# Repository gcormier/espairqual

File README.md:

# espairqual
espairqual is an ESP32 based [esphome](https://esphome.io/) interface for [PMSx003](https://esphome.io/components/sensor/pmsx003.html) and [Panasonic NA-GCJA5](https://na.industrial.panasonic.com/products/sensors/air-quality-gas-flow-sensors/lineup/laser-type-pm-sensor/series/123557/model/123559) particulate matter (PM) sensors.

It offers a plug and play solution to integrate air quality monitoring with home assistant. It provides 5V to the sensor and 3.3V to the internal electronics.

It can be powered by USC-C, or, by a wider range of input voltages on the screw terminals. It was designed for 24VAC, but will likely work with a slightly broader range
of both AC and DC input voltages. The absolute maximum voltage for the switching regulator is 40VDC, which means up to around 28VAC. The minimum DC is approximately 9VDC.

The PCB will fit inside a [Hammond 1593KBK](https://www.hammfg.com/part/1593KBK) case. You can either cut (CNC) or 3D-print the faceplates. I have superglue'd some magnets inside the case so it can stick to my ductwork, although this attenuates the WiFi signal *alot*.

## Programming
The USB-C port can be used to program. The first time, the reset button must be held. After this, all subsequent programming does not require access to the button.

There is also a header for the typical serial flashing with GPIO0(9) and EN exposed. It follows my [eflashy32](https://github.com/gcormier/eflashy32) pinout.

## Panasonic SN-GCJA5
I contributed native support for the SN-GCJA5 [to esphome](https://esphome.io/components/sensor/gcja5.html). While the PMS5003 is a good sensor, I did receive one dead-on-arrival from Aliexpress. The Panasonic sensor is cheaper, smaller, available from tier-1 distributors (eg. [Digikey](https://www.digikey.ca/en/products/detail/panasonic-electronic-components/SN-GCJA5/10443899)) and has a 5+ year life expectancy. It has internal compensation for the fan, photo diode and laser diode.

The connector is JST-GH (1.25mm) series.

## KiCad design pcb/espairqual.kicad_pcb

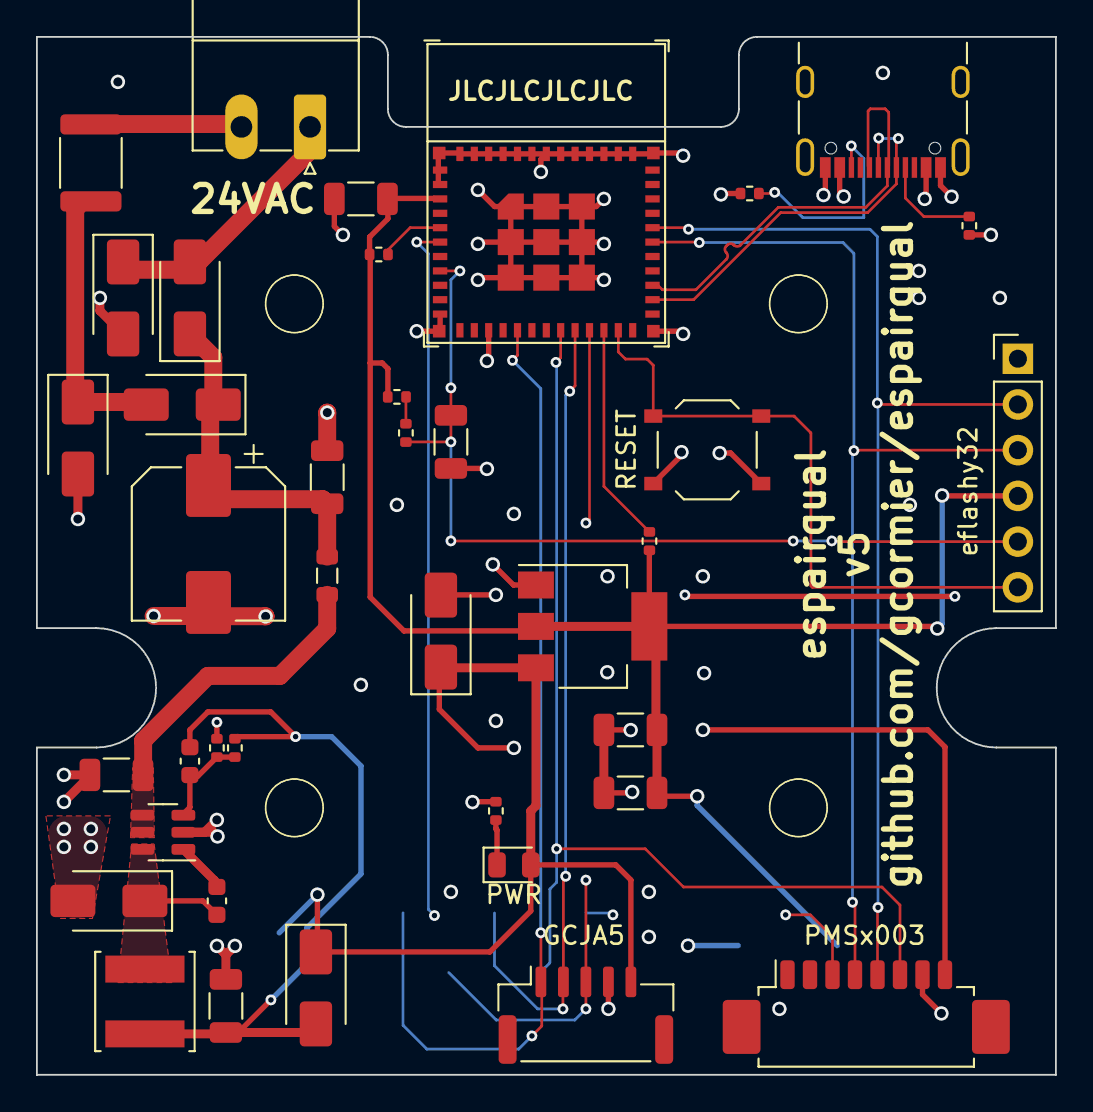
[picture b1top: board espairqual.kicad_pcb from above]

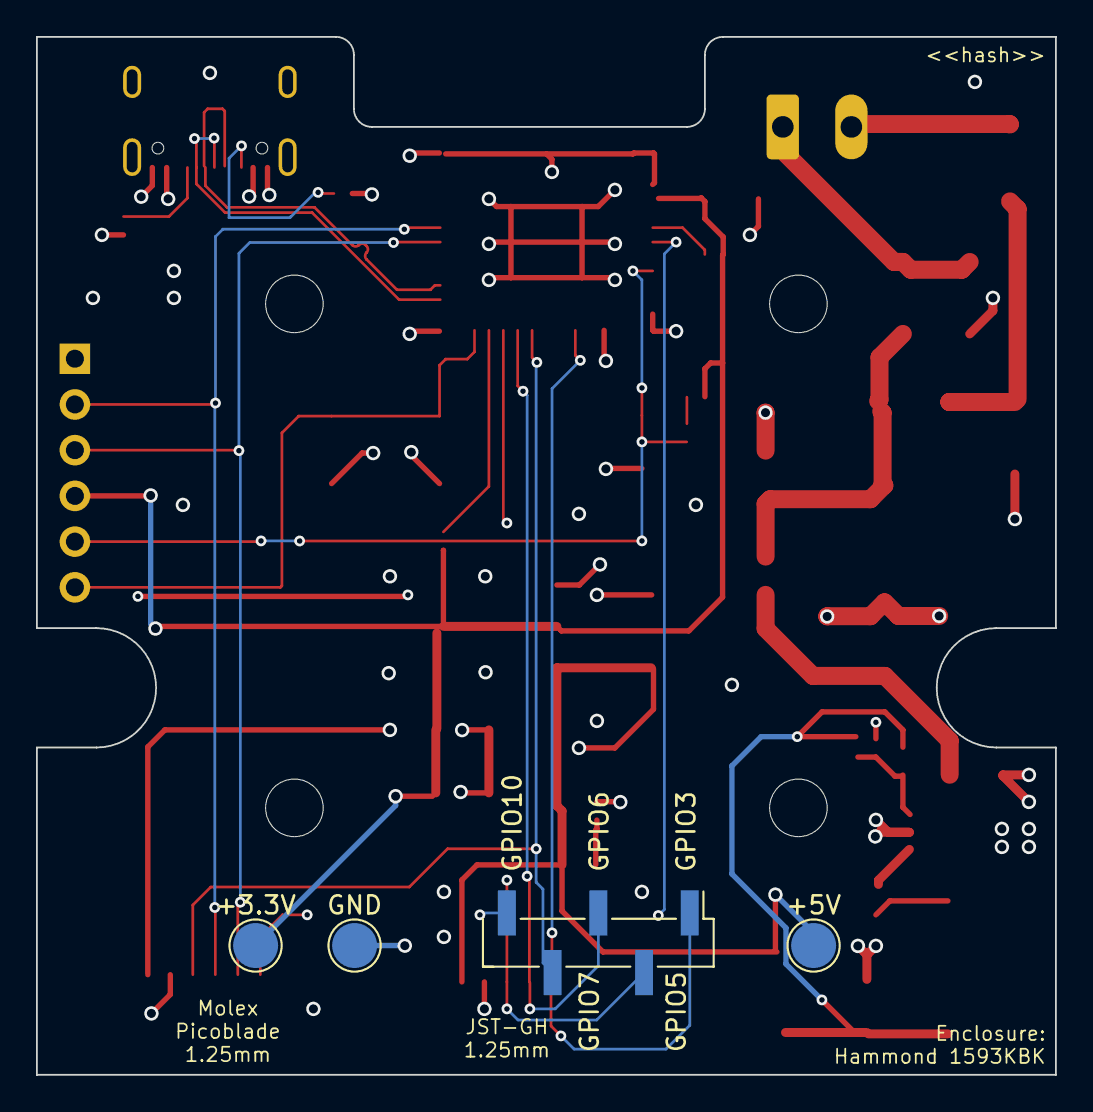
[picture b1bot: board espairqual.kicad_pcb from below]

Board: 4 copper layers, 56.6 x 57.7 mm, 47 parts (4 on the bottom side), 30 nets.

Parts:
C1, C6, C7, C8, C9, C11, C12: 10uF 50V; C_1206_3216Metric
C4: 0.1u 25v; C_0603_1608Metric
C5: 15nF; C_0603_1608Metric
C10: 100uF 50V; CP_Elec_8x10
D1, D2, D3, D4, D5, D6, D7: SS210; D_SMA
D8: PWR; LED_0805_2012Metric
F1: 140mA hold / 340mA trip mSMD014; Fuse_1812_4532Metric
FB1: 600@100MHz; L_0805_2012Metric
H1, H2, H3, H4: MountingHole; MountingHole_3.2mm_M3
J1: 24VAC; PhoenixContact_MC_1,5_2-G-3.81_1x02_P3.81mm_Horizontal
J2: PMSX003; Molex_PicoBlade_53261-0871_1x08-1MP_P1.25mm_Horizontal
J3: eflashy32; PinHeader_1x06_P2.54mm_Vertical
J4: USBC; USB_C_Receptacle_GCT_USB4105-xx-A_16P_TopMnt_Horizontal
J5: GCJA5; JST_GH_SM05B-GHS-TB_1x05-1MP_P1.25mm_Horizontal
J7: AUX; PinHeader_1x05_P2.54mm_Vertical_SMD_Pin1Left
L1: 6.8uH; L_Sunlord_SWPA5012S
R1, R3, R4, R5, R10, R11: 5k1; R_0402_1005Metric
R2, R6: 680; R_0402_1005Metric
R12: 3k9; R_0402_1005Metric
SW1: RESET; SW_Push_1P1T_XKB_TS-1187A
TP1: +5V; TestPoint_Pad_D2.5mm
TP2: GND; TestPoint_Pad_D2.5mm
TP3: +3.3V; TestPoint_Pad_D2.5mm
U1: BD9G101G; SOT-23-6
U3: AMS1117-3.3; SOT-223-3_TabPin2
U4: ESP32-C3-MINI-1

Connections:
+3V3: C8.1, C9.1, C11.2, J3.4, R3.1, R4.1, R5.1, TP3.1, U3.2 (VO), U4.3 (3V3)
+5V: D6.1 (K), D7.1 (K), D8.2 (A), J2.8, J5.5, TP1.1, U3.3 (VI)
/EN: C12.2, J3.5, R1.2, U4.8 (EN/CHIP_PU)
/FB: C4.2, R2.2, R12.1, U1.3 (FB)
/GPIO0: J3.6, SW1.1 (A), U4.23 (GPIO9)
/GPIO3: J2.3, J7.5, U4.6 (GPIO3/ADC1_CH3)
/GPIO5: J2.6, J7.4, U4.19 (GPIO5/ADC2_CH0)
/GPIO6: J5.2, J7.3, U4.20 (GPIO6)
/GPIO7: J5.3, J7.2, U4.21 (GPIO7)
/GPIO10: J5.1, J7.1, U4.16 (GPIO10)
/LX: C5.2, D1.1 (K), L1.1, U1.6 (LX)
/PMS_RXD: J2.5, J3.2, U4.31 (GPIO21/U0TXD)
/PMS_TXD: J2.4, J3.3, U4.30 (GPIO20/U0RXD)
/PWR5V: D6.2 (A), J4.A4 (VBUS), J4.A9 (VBUS), J4.B4 (VBUS), J4.B9 (VBUS)
/Vrec: C6.1, C10.1, D3.1 (K), D5.1 (K), FB1.2
D+: J4.A6 (D+), J4.B6 (D+), U4.27 (GPIO19/USB_D+)
D-: J4.A7 (D-), J4.B7 (D-), U4.26 (GPIO18/USB_D-)
GND: C1.2, C6.2, C7.2, C8.2, C9.2, C10.2, C11.1, C12.1, D1.2 (A), D2.2 (A), D4.2 (A), J2.7, J3.1, J4.A1 (GND), J4.A12 (GND), J4.B1 (GND), J4.B12 (GND), J5.4, R2.1, R6.2, R10.2, R11.2, SW1.2 (B), TP2.1, U1.2 (GND), U3.1 (GND), U4.1 (GND), U4.2 (GND), U4.11 (GND), U4.14 (GND), U4.36 (GND), U4.37 (GND), U4.38 (GND), U4.39 (GND), U4.40 (GND), U4.41 (GND), U4.42 (GND), U4.43 (GND), U4.44 (GND), U4.45 (GND), U4.46 (GND), U4.47 (GND), U4.48 (GND), U4.49 (GND), U4.50 (GND), U4.51 (GND), U4.52 (GND), U4.53 (GND)
unnamed: D2.1 (K), D3.2 (A), F1.2
unnamed: D4.1 (K), D5.2 (A), J1.1
unnamed: C4.1, C7.1, D7.2 (A), L1.2, R12.2
unnamed: D8.1 (K), R6.1
unnamed: F1.1, J1.2
unnamed: J4.A5 (CC1), R10.1
unnamed: J4.B5 (CC2), R11.1
unnamed: R1.1, R3.2
unnamed: C5.1, U1.1 (BST)
unnamed: C1.1, FB1.1, U1.4 (EN), U1.5 (VIN)
unnamed: R4.2, U4.5 (GPIO2/ADC1_CH2)
unnamed: R5.2, U4.22 (GPIO8)

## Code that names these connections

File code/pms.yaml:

# Sample espairqual config using the PlanTower PM3 sensor
esp32:
  board: esp32-c3-devkitm-1

esphome:
  name: plan-pm3
  on_boot:
    then:
      - output.turn_on: gpio3_output
      - output.turn_on: gpio5_output

wifi:
  ssid: !secret wifi_ssid
  password: !secret wifi_password

  # Enable fallback hotspot (captive portal) in case wifi connection fails
  ap:
    ssid: "espairqualFallback"
    password: "espairqual"


# Enable logging
# do not use serial logging
logger:
  level: VERBOSE
  baud_rate: 0

api:

ota:


uart:
  rx_pin: GPIO20
  tx_pin: GPIO21
  baud_rate: 9600

output:
  - platform: gpio
    pin: GPIO3
    id: gpio3_output

  - platform: gpio
    pin: GPIO5
    id: gpio5_output


sensor:
  - platform: pmsx003
    #type: PMSX003
    pm_1_0:
      name: "Particulate Matter <1.0µm Concentration"
    pm_10_0:
      name: "Particulate Matter <10.0µm Concentration"
    pm_2_5:
      name: "Particulate Matter <2.5µm Concentration"
    
    type: PMS5003T 
    temperature:
      name: "PMS Temperature"
    humidity:
      name: "PMS Humidity"
    update_interval: 60s

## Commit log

2022-12-01 actions
2022-12-01 ignore
2022-12-01 esp32 time
2022-12-01 caps
2022-12-13 yaml
2022-12-21 update workflow
2022-12-21 inner
2022-12-21 basic readme
2022-12-21 docs
2022-12-21 render
2022-12-21 change Z
2022-12-21 yes?
2022-12-21 resize
2022-12-21 auto image?
2022-12-21 abort!
2022-12-21 filename
2023-06-21 tweak
2023-06-21 touchup before fab
2023-06-21 panel
2023-06-21 fix actions
2023-06-21 gerber filename
2023-06-25 doc update for v4
2023-06-25 4layery
2023-06-25 layerCasE
2023-07-08 update sample
2023-09-28 udpates
2023-09-28 new render
2023-09-30 some tweaks
2023-10-01 test some panel
2023-10-01 norendernostep
2023-10-01 ignore temp
2023-10-01 cleanup
2023-10-01 tindie badge
2023-10-04 final tweaks
2023-10-04 edgecuts for panel
2023-10-08 pipeline
